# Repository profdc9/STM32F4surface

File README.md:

This is a Bluepill pinout-compatible devboard for the STM32F405RGT6 LQFP-64 microcontroller.
It uses surface mount parts and includes the JLCPCB/LCSC part BOM.
This material is copyrighted by Daniel Marks (KW4TI) and licensed under
the Creative Commons License CC-BY-SA 4.0.  Software is copyrighted using the zlib
open-source license.

There are two BOMs:

STM32alt-BOM-STM32F4.xlsx is for populating with a STM32F405RGT6
STM32alt-BOM-STM32F1.xlsx is for populating with a STM32F103RET6

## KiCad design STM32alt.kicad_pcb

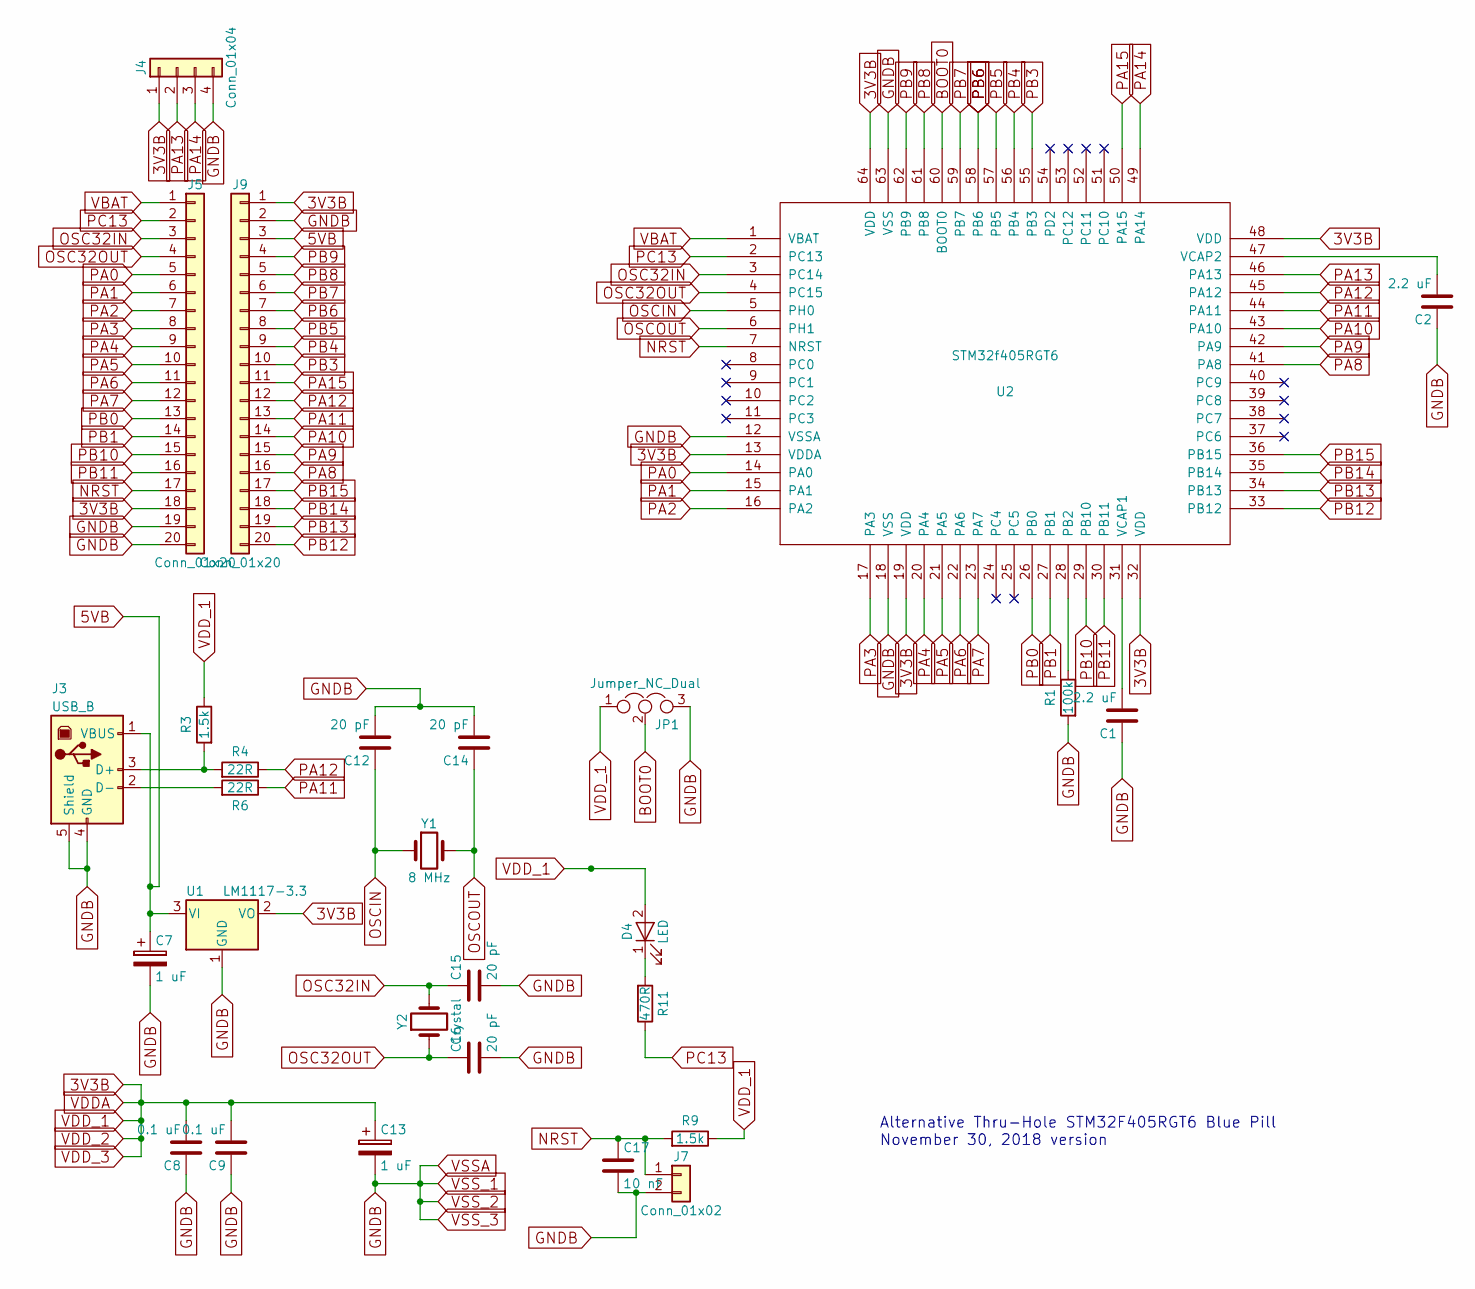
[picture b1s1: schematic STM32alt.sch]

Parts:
C1, C2: 2.2 uF; C_0805_HandSoldering; LCSC C49217
C7, C13: 1 uF; C_0805_HandSoldering; LCSC C28323
C8, C9: 0.1 uF; C_0805_HandSoldering; LCSC C49678
C12, C14, C15, C16: 20 pF; C_0805_HandSoldering; LCSC C1798
C17: 10 nF; C_0805_HandSoldering; LCSC C1710
D4: LED; LED_0805_HandSoldering; LCSC C84256
J3: USB_B
J4: Conn_01x04; Pin_Header_Straight_1x04_Pitch2.54mm
J5, J9: Conn_01x20; Pin_Header_Straight_1x20_Pitch2.54mm
J7: Conn_01x02; SW_PUSH_6mm
JP1: Jumper_NC_Dual; Pin_Header_Straight_1x03_Pitch2.54mm
R1: 100k; R_0805_HandSoldering; LCSC C17407
R3, R9: 1.5k; R_0805_HandSoldering; LCSC C4310
R4, R6: 22R; R_0805_HandSoldering; LCSC C17561
R11: 470R; R_0805_HandSoldering; LCSC C17710
U1: LM1117-3.3; SOT-223-3_TabPin2; LCSC C6186
U2: STM32f405RGT6; LQFP-64_10x10mm_Pitch0.5mm; LCSC C15742
Y1: 8 MHz; Crystal_SMD_5032-2pin_5.0x3.2mm; LCSC C115962
Y2: Crystal; Crystal_SMD_3215-2pin_3.2x1.5mm; LCSC C32346

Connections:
3V3B: C8.2, C9.2, C13.1, D4.2 (A), J4.1, J5.18, J9.1, JP1.1, R3.1, R9.1, U1.2 (VO), U2.13 (VDDA), U2.19 (VDD), U2.32 (VDD), U2.48 (VDD), U2.64 (VDD)
5VB: C7.1, J3.1 (VBUS), J9.3, U1.3 (VI)
BOOT0: JP1.2, U2.60 (BOOT0)
GNDB: C1.1, C2.1, C7.2, C8.1, C9.1, C12.2, C13.2, C14.2, C15.2, C16.2, C17.2, J3.4 (GND), J3.5 (Shield), J4.4, J5.19, J5.20, J7.2, J9.2, JP1.3, R1.2, U1.1 (GND), U2.12 (VSSA), U2.18 (VSS), U2.63 (VSS)
NRST: C17.1, J5.17, J7.1, R9.2, U2.7 (NRST)
unnamed: C1.2, U2.31 (VCAP1)
unnamed: C2.2, U2.47 (VCAP2)
unnamed: D4.1 (K), R11.2
unnamed: J3.2 (D-), R6.2
unnamed: J3.3 (D+), R3.2, R4.2
unnamed: R1.1, U2.28 (PB2)
OSC32IN: C15.1, J5.3, U2.3 (PC14), Y2.2
OSC32OUT: C16.1, J5.4, U2.4 (PC15), Y2.1
OSCIN: C12.1, U2.5 (PH0), Y1.1
OSCOUT: C14.1, U2.6 (PH1), Y1.2
PA0: J5.5, U2.14 (PA0)
PA1: J5.6, U2.15 (PA1)
PA2: J5.7, U2.16 (PA2)
PA3: J5.8, U2.17 (PA3)
PA4: J5.9, U2.20 (PA4)
PA5: J5.10, U2.21 (PA5)
PA6: J5.11, U2.22 (PA6)
PA7: J5.12, U2.23 (PA7)
PA8: J9.16, U2.41 (PA8)
PA9: J9.15, U2.42 (PA9)
PA10: J9.14, U2.43 (PA10)
PA11: J9.13, R6.1, U2.44 (PA11)
PA12: J9.12, R4.1, U2.45 (PA12)
PA13: J4.2, U2.46 (PA13)
PA14: J4.3, U2.49 (PA14)
PA15: J9.11, U2.50 (PA15)
PB0: J5.13, U2.26 (PB0)
PB1: J5.14, U2.27 (PB1)
PB3: J9.10, U2.55 (PB3)
PB4: J9.9, U2.56 (PB4)
PB5: J9.8, U2.57 (PB5)
PB6: J9.7, U2.58 (PB6)
PB7: J9.6, U2.59 (PB7)
PB8: J9.5, U2.61 (PB8)
PB9: J9.4, U2.62 (PB9)
PB10: J5.15, U2.29 (PB10)
PB11: J5.16, U2.30 (PB11)
PB12: J9.20, U2.33 (PB12)
PB13: J9.19, U2.34 (PB13)
PB14: J9.18, U2.35 (PB14)
PB15: J9.17, U2.36 (PB15)
PC13: J5.2, R11.1, U2.2 (PC13)
VBAT: J5.1, U2.1 (VBAT)

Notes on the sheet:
Alternative Thru-Hole STM32F405RGT6 Blue Pill November 30, 2018 version

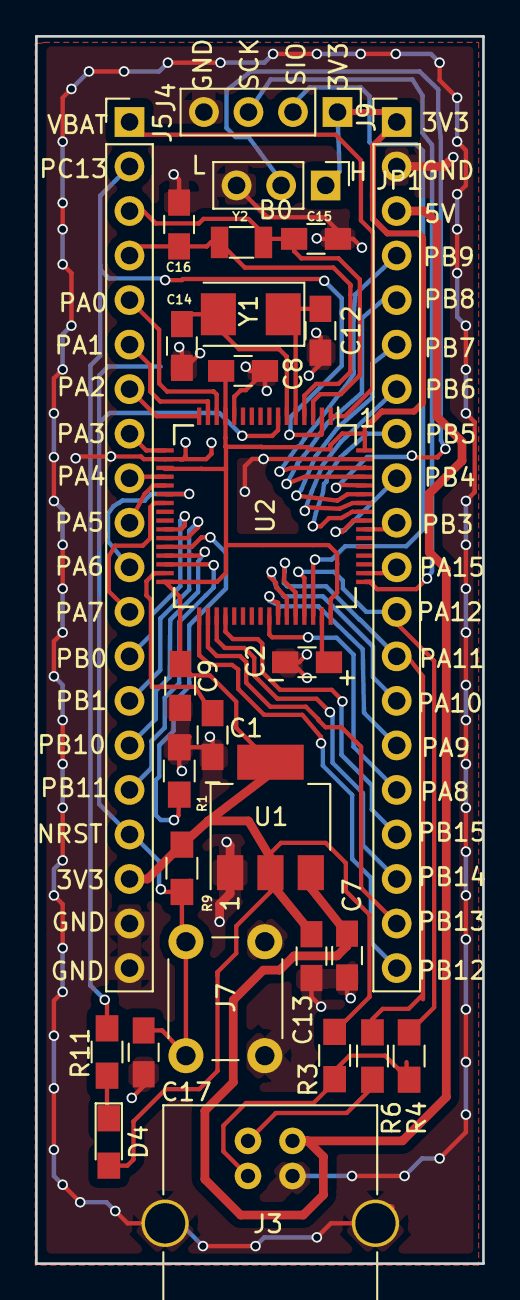
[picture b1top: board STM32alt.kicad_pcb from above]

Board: 2 copper layers, 25.5 x 70.0 mm, 28 parts (0 on the bottom side), 48 nets.
